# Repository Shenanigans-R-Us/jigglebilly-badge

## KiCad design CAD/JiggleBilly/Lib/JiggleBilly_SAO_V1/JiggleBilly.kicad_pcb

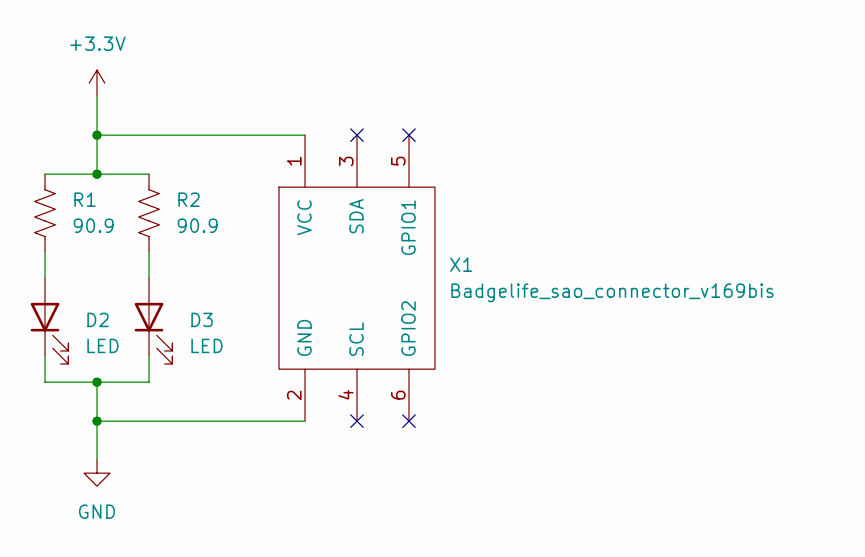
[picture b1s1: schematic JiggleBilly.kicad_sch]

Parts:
D2, D3: LED; LED_Osram_Lx_P47F_D2mm_ReverseMount_Proper_Mask Only; MPN XZVG45WT-9
R1, R2: 90.9; R_0805_2012Metric_Pad1.20x1.40mm_HandSolder; MPN RMCF0805FT90R9
X1: Badgelife_sao_connector_v169bis; Badgelife-SAOv169-SAO_Side_B.SLK; MPN CH87062V200

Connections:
+3.3V: R1.1, R2.1, X1.1 (VCC)
GND: D2.1 (K), D3.1 (K), X1.2 (GND)
unnamed: D2.2 (A), R1.2
unnamed: D3.2 (A), R2.2

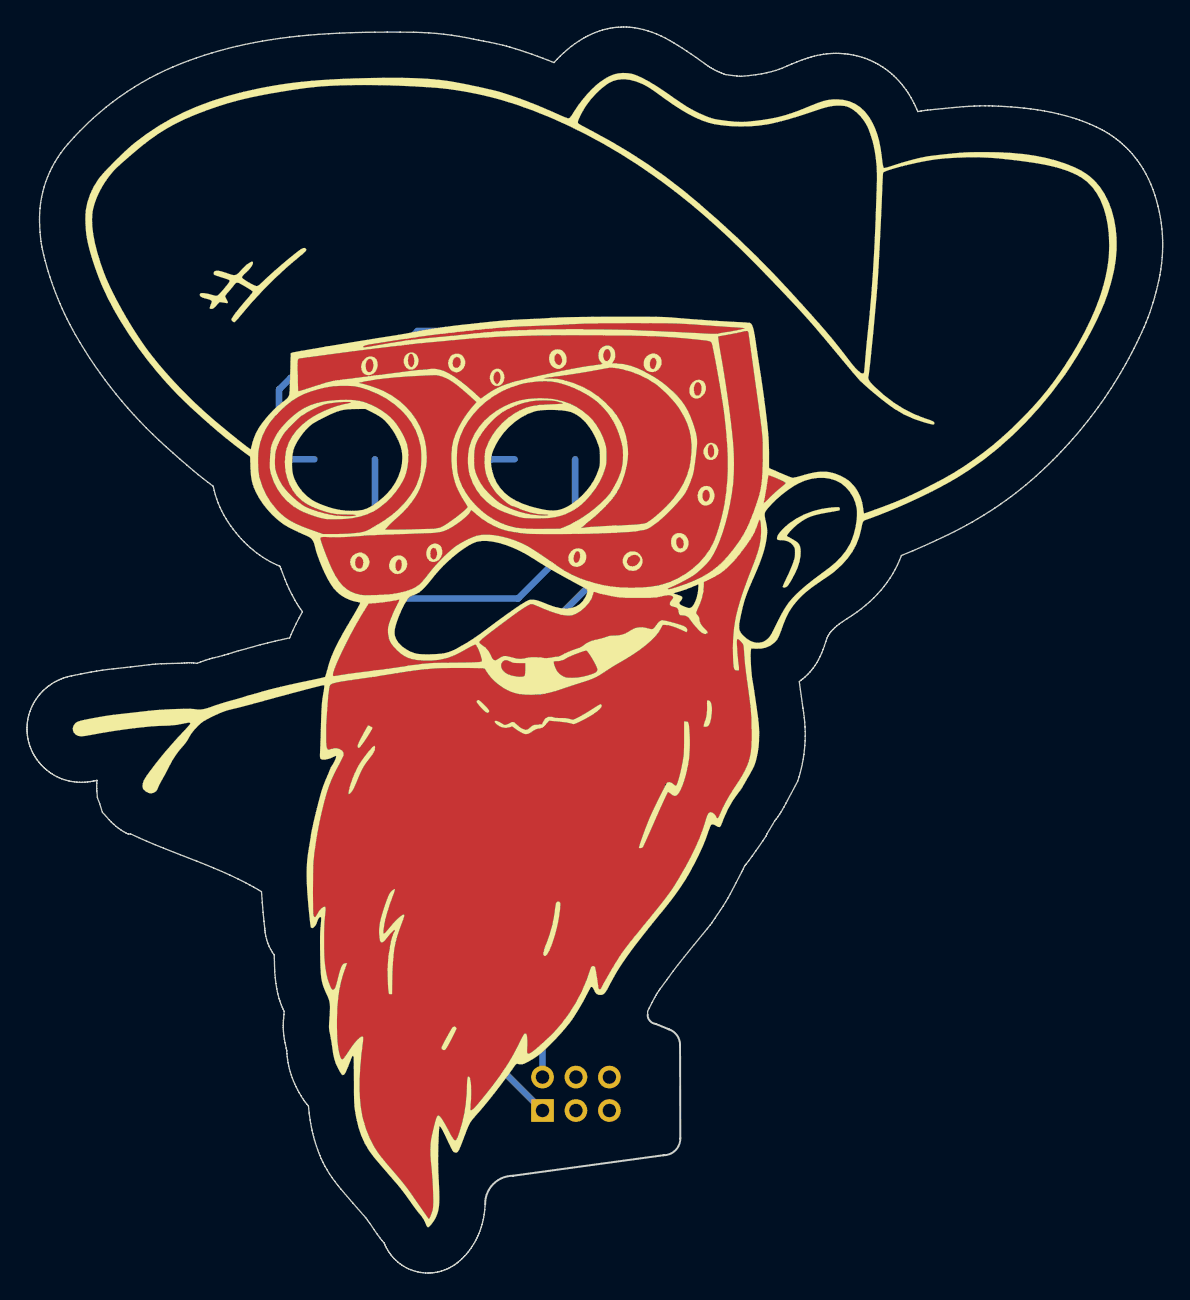
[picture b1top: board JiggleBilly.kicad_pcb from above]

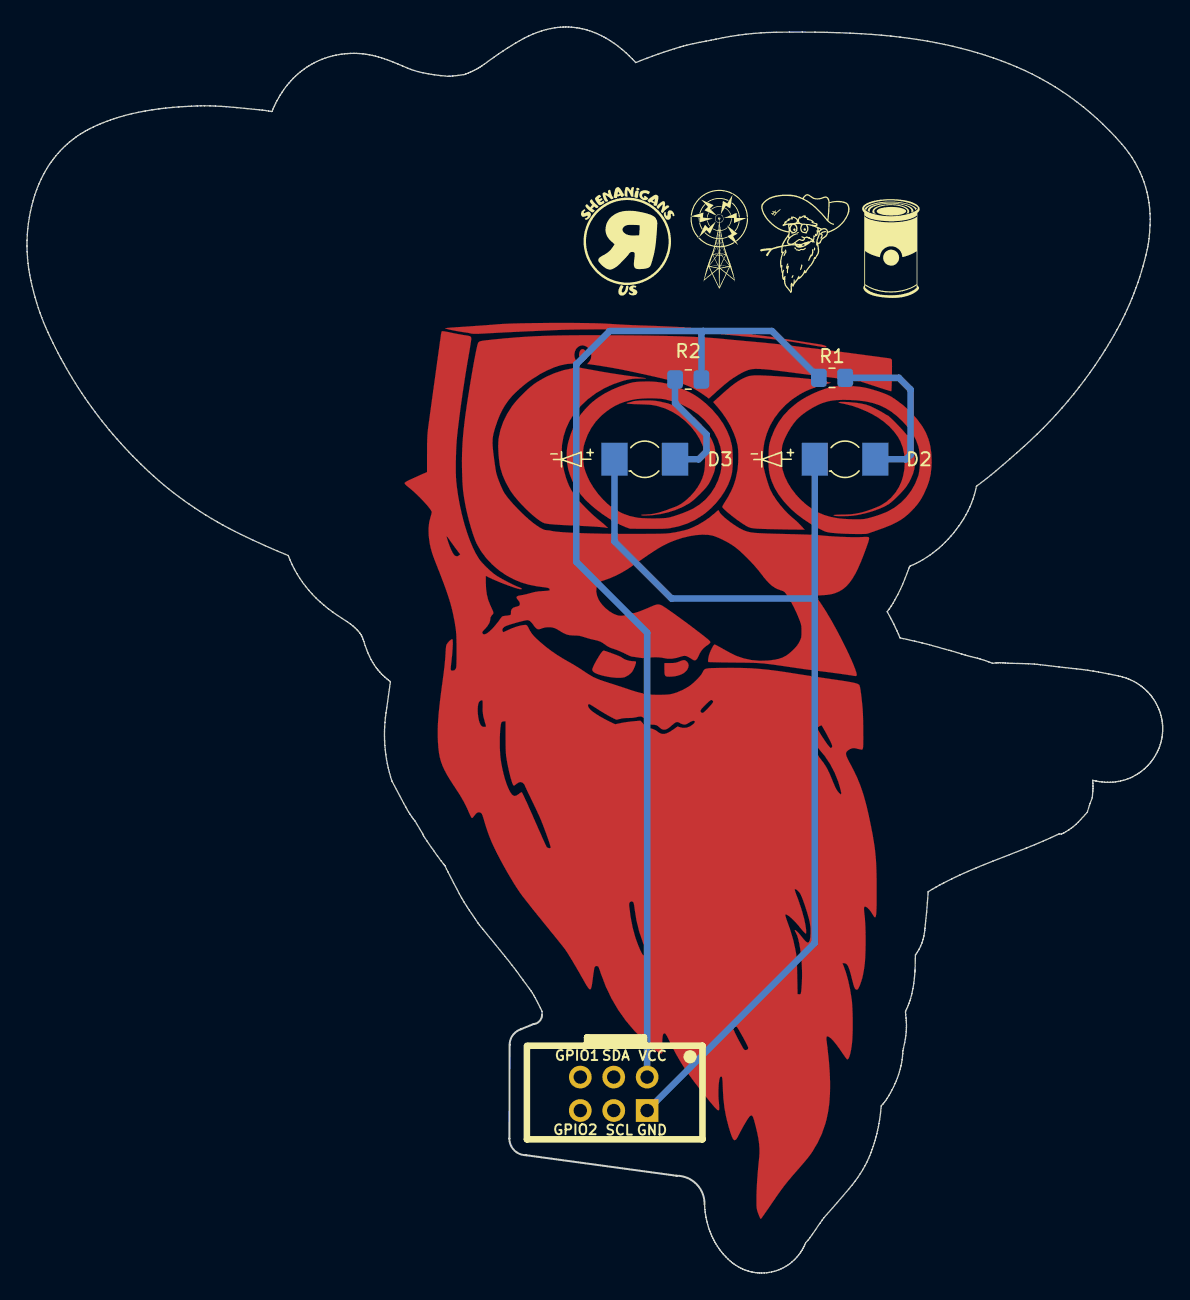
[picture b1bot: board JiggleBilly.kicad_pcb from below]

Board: 2 copper layers, 86.3 x 94.7 mm, 5 parts (4 on the bottom side), 4 nets.

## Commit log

2024-01-19 art file
2024-01-19 adding stamp files, should be ready use
2024-01-19 Use where ever you want
2024-01-19 Front of badge, Ready to move to next stage
2024-01-19 Reference images and readme
2024-01-19 Goggles front, ready to move to the next stage
2024-01-19 Work in progress, still need work
2024-01-23 Jigglebilly full color reference.
2024-01-31 Start of the artwork conversion
2024-05-29 Added JiggleBilly Badge Files
    Kicad files for JiggleBilly
2024-05-29 Goggles KiCad Files
    Goggles KiCad Files
2024-06-18 CAD Files added
    Silkscreen, F.Soldermask, B.Soldermask, Hasl, and PCB setup.
    Electronics need to be added still.
2024-07-03 added schematics, footprints, edited PCB, needs looked at for errors
2024-07-03 Moved SAO connector and rerouted traces
    Moved the SAO connector so it would not conflict with the beard pad
2024-07-03 Added submodule
    Added BP library as a sub module. Change the foorprint pathto be generic to the project. Added lockfile to the ignore
2024-07-03 Update .gitignore
    Ignore backups folder
2024-07-03 Update part info
    Updated part info for BOM generaton
2024-07-03 Create BOM and Gerbers
    Changes to help with BOM creation.
    BOM added
    Gerber and drill outputs added for JLCPCB
2024-07-03 Changes from sending PCBs for Estimate
2024-07-10 updated bom
2024-07-10 Added production files for solder stencil
